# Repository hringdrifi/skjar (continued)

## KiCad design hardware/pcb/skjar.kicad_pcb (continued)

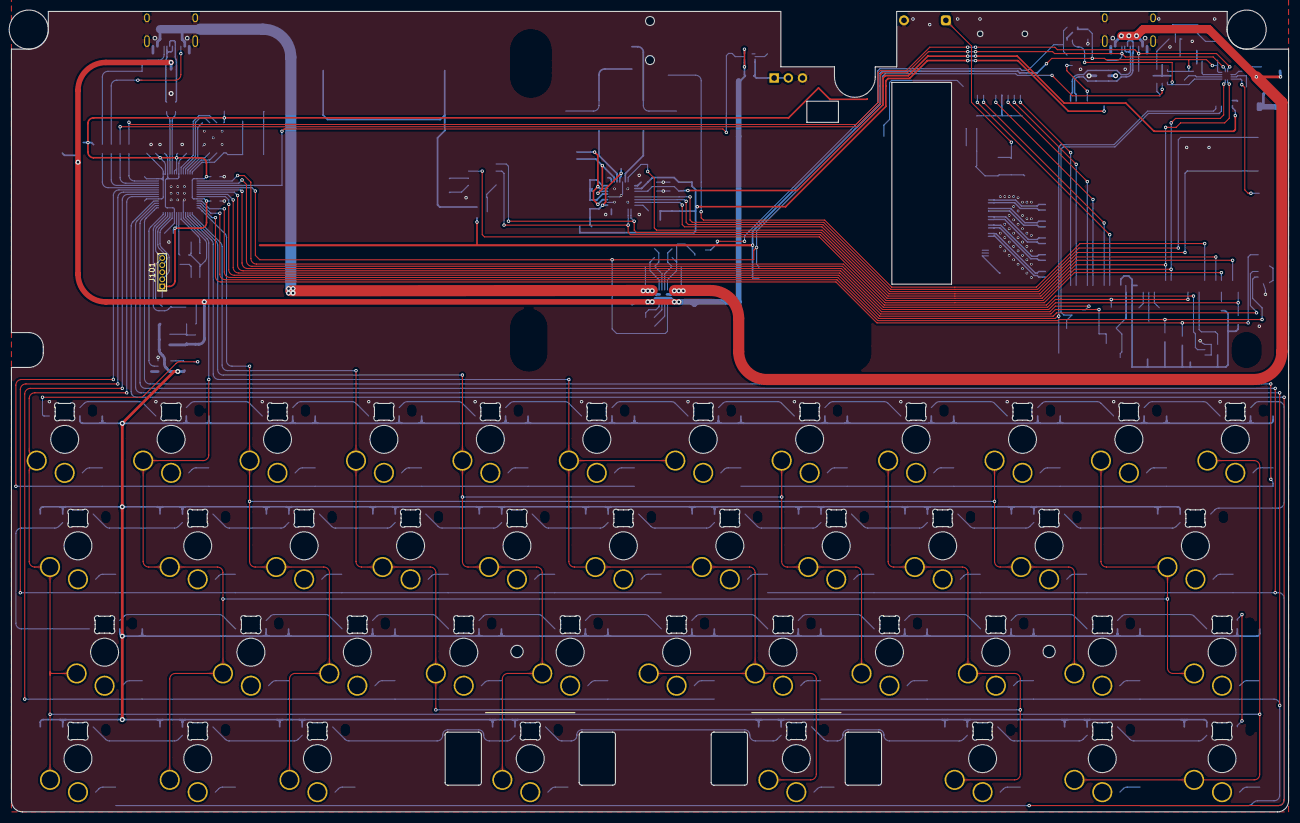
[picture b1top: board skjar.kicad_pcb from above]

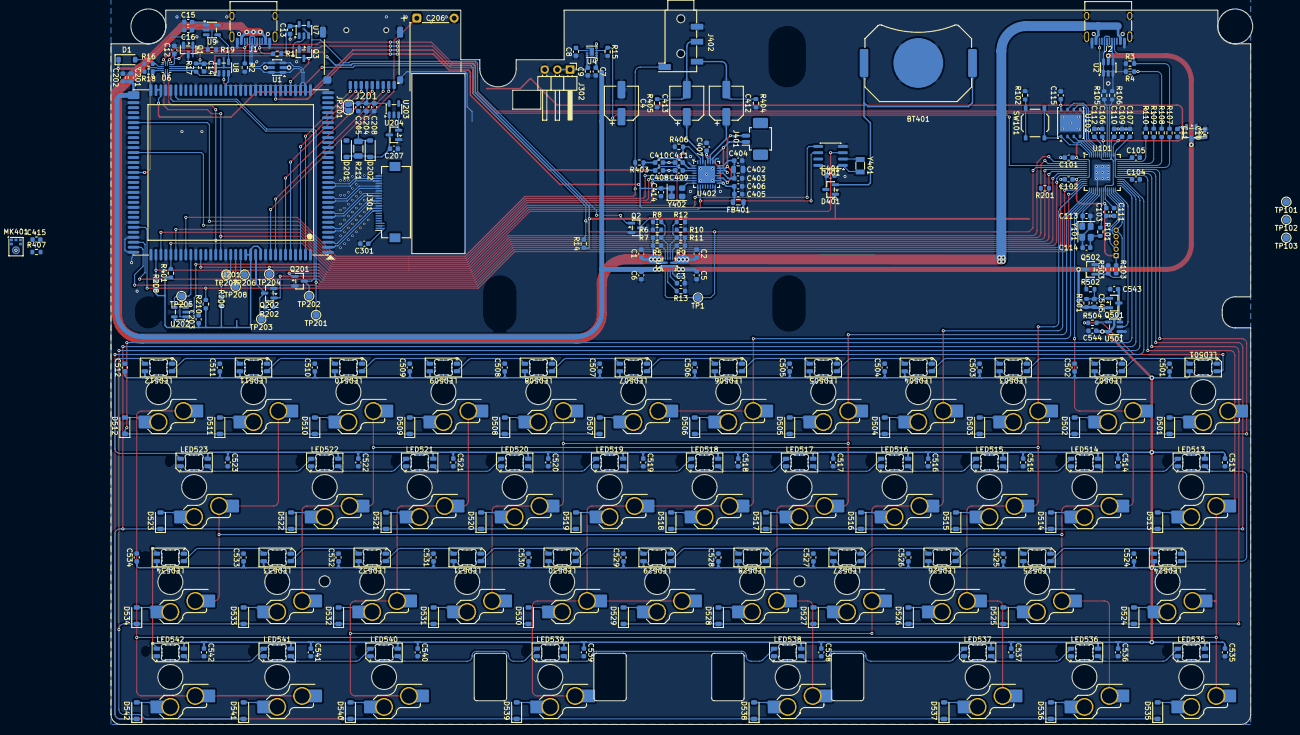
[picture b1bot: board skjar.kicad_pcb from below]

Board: 2 copper layers, 228.6 x 143.3 mm, 332 parts (325 on the bottom side), 215 nets.

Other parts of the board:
DISP1: Waveshare_8.8-DSI-TOUCH-A_Studs
DISP2: Waveshare_8.8inch_DSI_LCD_Check
H8, H9: MountingHole_M2_CaseBoss
STAB1: CPG1353G24D01_2.75U
STAB2: CPG1353G24D01_2.25U

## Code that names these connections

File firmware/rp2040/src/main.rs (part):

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))]
compile_error!("feature の `pico`、`xiao`、`skjar` は、どれか 1 つだけを選ぶ（`xiao` と `skjar` は --no-default-features と一緒に）");

// キー入力の I²C。SKJÁR は I2C0（GPIO24 / 25）。Pico と XIAO では GPIO24 / 25 が外に出ていないので
// I2C1（GPIO26 / 27。XIAO では D0 / D1）を使う。
#[cfg(feature = "skjar")]
type KbI2c = embassy_rp::peripherals::I2C0;
#[cfg(not(feature = "skjar"))]
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    // ログ（USB の仮想シリアル）
    spawner.spawn(usb_task(Driver::new(p.USB, Irqs)).unwrap());

    // KB_INT（GPIO13。XIAO では D2 の GPIO28）：Low で CM0 に知らせる。オープンドレインを真似る（hid_i2c 参照）。
    #[cfg(not(feature = "xiao"))]
    hid_i2c::init_int_pin(Flex::new(p.PIN_13));
    #[cfg(feature = "xiao")]
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    let i2c = I2cSlave::new(p.I2C1, p.PIN_27, p.PIN_26, Irqs, i2c_config);
    spawner.spawn(hid_i2c_task(i2c).unwrap());

    // CM0 との UART（UART0：GPIO16 TX → CM0 の GPIO15、GPIO17 RX ← CM0 の GPIO14。
    // XIAO では GPIO16 / 17 が基板の LED なので、D6 の GPIO0 TX と D7 の GPIO1 RX）。
    // TX は CM0 の 3.3V で動くバッファを通るので、CM0 が OFF でも電流は流れ込まない。
    // RX には内部のプルを付けない（embassy-rp の初期化はプルを有効にしない）。
    static UART_TX_BUF: StaticCell<[u8; 256]> = StaticCell::new();
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    rmk::state::set_usb_state(UsbState::Configured);
    spawner.spawn(report_bridge_task().unwrap());

    // キーの RGB（GPIO14 RGB_DATA を PIO0 で、GPIO15 RGB_EN は High で電源 ON。初めは OFF）。
    // Pico で試すときは、同じ GP14 / GP15 に WS2812 のテープ LED などをつなぐ
    let mut pio = Pio::new(p.PIO0, Irqs);
    let ws2812 = PioWs2812Program::new(&mut pio.common);
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    // RMK の COL2ROW は、列を High に駆動して行を読む（行はプルダウン）。
    #[cfg(not(feature = "xiao"))]
    let rows = [
        Input::new(p.PIN_12, Pull::Down), // ROW0
        Input::new(p.PIN_6, Pull::Down),  // ROW1
        Input::new(p.PIN_11, Pull::Down), // ROW2
        Input::new(p.PIN_7, Pull::Down),  // ROW3
        Input::new(p.PIN_10, Pull::Down), // ROW4
        Input::new(p.PIN_8, Pull::Down),  // ROW5
        Input::new(p.PIN_9, Pull::Down),  // ROW6
    ];
    #[cfg(not(feature = "xiao"))]
    let cols = [
        Output::new(p.PIN_5, Level::Low), // COL0
        Output::new(p.PIN_4, Level::Low), // COL1
        Output::new(p.PIN_3, Level::Low), // COL2
        Output::new(p.PIN_2, Level::Low), // COL3
        Output::new(p.PIN_1, Level::Low), // COL4
        Output::new(p.PIN_0, Level::Low), // COL5
    ];
    // XIAO：外に出ている 6 本を 3 行 × 3 列にして、ROW2・ROW4・ROW6 の 1・2・5 列目（9 キー）を試す。
    // 親指の段（ROW6）の 5 列目がレイヤー 2（押し続ける）なので、レイヤー 2 の音量キー（ROW2）と
    // USER キー（ROW4）も試せる。ほかの行と列は、外に出ていない（何もつながっていない）ピンにする。
    // 行はプルダウンなので押されることはない。GPIO11 / 12（基板の RGB LED の電源とデータ）と
    // 16 / 17 / 25（基板の LED）は避ける
    #[cfg(feature = "xiao")]
    let rows = [
        Input::new(p.PIN_10, Pull::Down), // ROW0  （出ていない）
        Input::new(p.PIN_8, Pull::Down),  // ROW1  （出ていない）
        Input::new(p.PIN_6, Pull::Down),  // ROW2  D4：A S G（レイヤー 2 で Mute、音量 −）
        Input::new(p.PIN_9, Pull::Down),  // ROW3  （出ていない）
        Input::new(p.PIN_7, Pull::Down),  // ROW4  D5：Z X B（レイヤー 2 で USER0、USER1）
        Input::new(p.PIN_13, Pull::Down), // ROW5  （出ていない）
        Input::new(p.PIN_29, Pull::Down), // ROW6  D3：LGui LAlt Space（押し続けるとレイヤー 2）
    ];
    #[cfg(feature = "xiao")]
    let cols = [
        Output::new(p.PIN_20, Level::Low), // COL0  （出ていない）
        Output::new(p.PIN_4, Level::Low),  // COL1  D9
        Output::new(p.PIN_3, Level::Low),  // COL2  D10
        Output::new(p.PIN_18, Level::Low), // COL3  （出ていない）
        Output::new(p.PIN_19, Level::Low), // COL4  （出ていない）
        Output::new(p.PIN_2, Level::Low),  // COL5  D8
    ];
    let mut matrix = Matrix::<_, _, _, MATRIX_ROW, COL, true>::new(rows, cols, DefaultDebouncer::new());

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
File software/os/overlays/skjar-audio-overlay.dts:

// SKJAR audio: TLV320DAC3100 on I2C1 (0x18) and I2S (GPIO18/19/21)
//
// Build and install (on the CM0):
//   dtc -@ -I dts -O dtb -o skjar-audio.dtbo skjar-audio-overlay.dts
//   sudo cp skjar-audio.dtbo /boot/firmware/overlays/
//
// config.txt:
//   dtparam=i2c_arm=on
//   dtparam=i2s=on
//   dtparam=audio=off
//   dtoverlay=skjar-audio
//
// A 12 MHz oscillator (Y402) drives MCLK and the codec is the I2S clock
// master; the Pi only receives BCLK and LRCLK. simple-audio-card calls
// set_sysclk() with clk_id 0 (MCLK), which is what this setup needs, so
// the stock tlv320aic31xx driver works as is. See README.md.
//
// GPIO17 (HP_DET) is low when a plug is inserted. GPIO22 is the codec
// reset (active low).

/dts-v1/;
/plugin/;

/ {
	compatible = "brcm,bcm2835";

	// I2S, codec drives BCLK and LRCLK
	fragment@0 {
		target = <&i2s_clk_consumer>;
		__overlay__ {
			status = "okay";
		};
	};

	// Fixed supplies (all always on)
	fragment@1 {
		target-path = "/";
		__overlay__ {
			vdd_5v_spk: skjar-audio-5v {
				compatible = "regulator-fixed";
				regulator-name = "skjar-spkvdd";
				regulator-min-microvolt = <5000000>;
				regulator-max-microvolt = <5000000>;
				regulator-always-on;
			};

			vdd_3v3_audio: skjar-audio-3v3 {
				compatible = "regulator-fixed";
				regulator-name = "skjar-avdd";
				regulator-min-microvolt = <3300000>;
				regulator-max-microvolt = <3300000>;
				regulator-always-on;
			};

			vdd_1v8_audio: skjar-audio-1v8 {
				compatible = "regulator-fixed";
				regulator-name = "skjar-dvdd";
				regulator-min-microvolt = <1800000>;
				regulator-max-microvolt = <1800000>;
				regulator-always-on;
			};
		};
	};

	// Codec on I2C1 (PCF8563 at 0x51 is added by i2c-rtc,pcf8563)
	fragment@2 {
		target = <&i2c1>;
		__overlay__ {
			#address-cells = <1>;
			#size-cells = <0>;
			status = "okay";

			dac3100: codec@18 {
				compatible = "ti,tlv320dac3100";
				reg = <0x18>;
				#sound-dai-cells = <0>;
				reset-gpios = <&gpio 22 1>;	// GPIO_ACTIVE_LOW

				HPVDD-supply = <&vdd_3v3_audio>;
				SPRVDD-supply = <&vdd_5v_spk>;
				SPLVDD-supply = <&vdd_5v_spk>;
				AVDD-supply = <&vdd_3v3_audio>;
				IOVDD-supply = <&vdd_3v3_audio>;
				DVDD-supply = <&vdd_1v8_audio>;

				status = "okay";
			};
		};
	};

	// HP_DET: input, internal pull off (the default pull-down on
	// GPIO17 would fight the 100k board pull-up)
	fragment@3 {
		target = <&gpio>;
		__overlay__ {
			skjar_audio_pins: skjar_audio_pins {
				brcm,pins = <17>;
				brcm,function = <0>;	// input
				brcm,pull = <0>;	// none
			};
		};
	};

	fragment@4 {
		target = <&sound>;
		sound_overlay: __overlay__ {
			compatible = "simple-audio-card";
			simple-audio-card,name = "skjar";
			simple-audio-card,format = "i2s";
			simple-audio-card,bitclock-master = <&codec_dai>;
			simple-audio-card,frame-master = <&codec_dai>;

			pinctrl-names = "default";
			pinctrl-0 = <&skjar_audio_pins>;

			// Creates the "Headphones Jack" control and enables
			// the Headphones pin only while a plug is in
			simple-audio-card,hp-det-gpios = <&gpio 17 1>;	// active low

			simple-audio-card,widgets =
				"Headphone", "Headphones",
				"Speaker", "Internal Speaker";
			simple-audio-card,routing =
				"Headphones", "HPL",
				"Headphones", "HPR",
				"Internal Speaker", "SPK";
			// "Internal Speaker Switch", muted from userspace
			// while "Headphones Jack" is on
			simple-audio-card,pin-switches = "Internal Speaker";

			status = "okay";

			simple-audio-card,cpu {
				sound-dai = <&i2s_clk_consumer>;
			};

			// MCLK from Y402. No mclk-fs: the rate is fixed and
			// the driver picks its PLL settings from this value.
			codec_dai: simple-audio-card,codec {
				sound-dai = <&dac3100>;
				system-clock-frequency = <12000000>;
			};
		};
	};

	__overrides__ {
		card-name = <&sound_overlay>, "simple-audio-card,name";
	};
};
